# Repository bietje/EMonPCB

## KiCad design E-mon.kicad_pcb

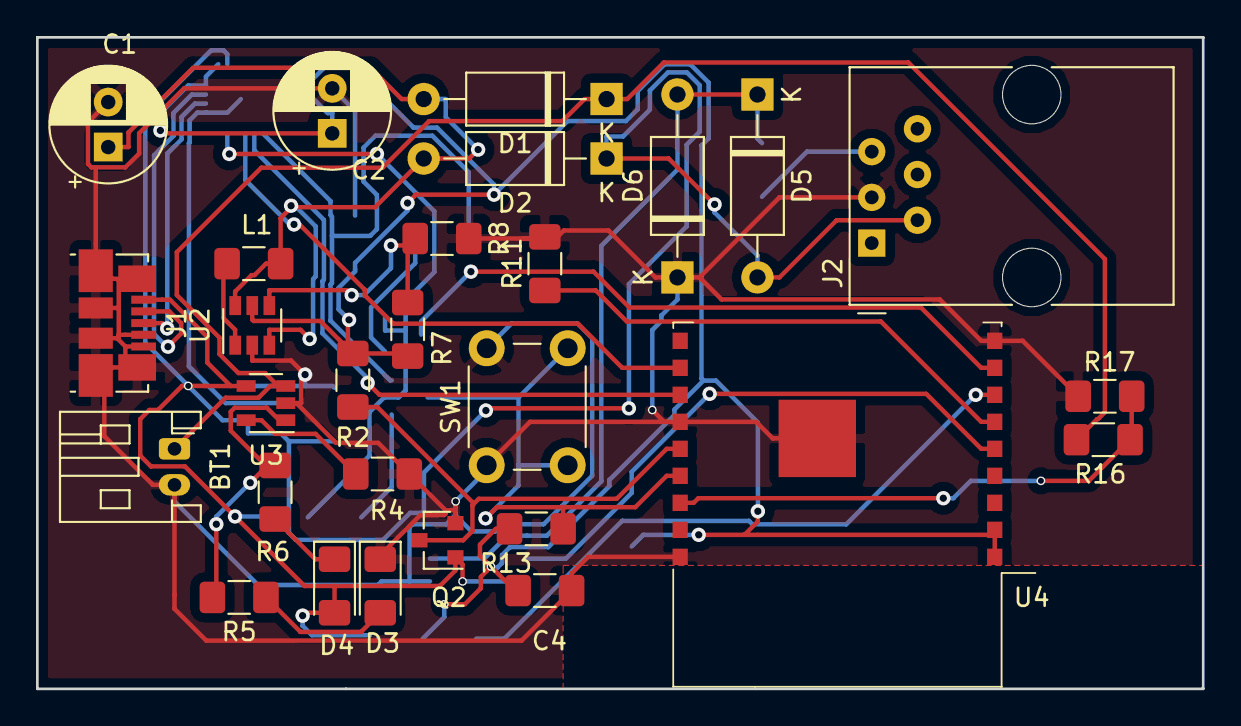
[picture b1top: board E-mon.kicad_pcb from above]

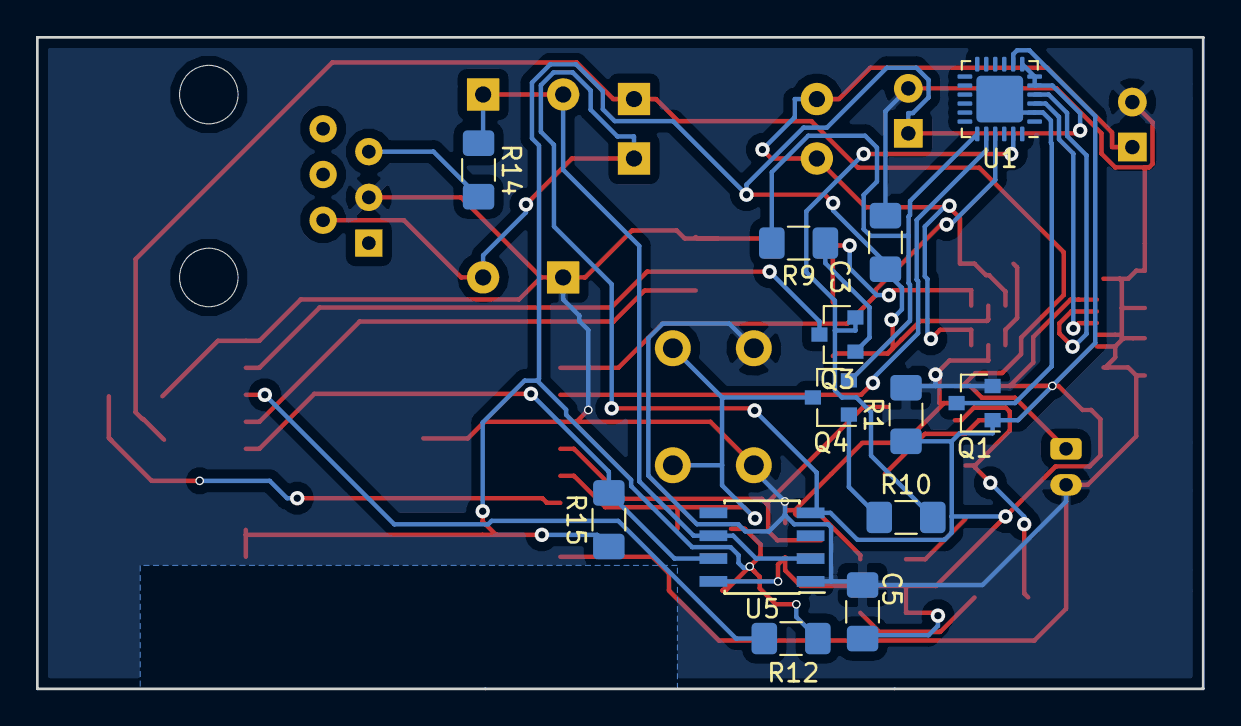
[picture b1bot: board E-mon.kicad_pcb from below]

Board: 2 copper layers, 64.8 x 36.2 mm, 41 parts (13 on the bottom side), 29 nets.

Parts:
BT1: Battery_Cell; JST_PH_S2B-PH-K_1x02_P2.00mm_Horizontal
C1: 4.7uF; CP_Radial_D6.3mm_P2.50mm
C2: 10uF; CP_Radial_D6.3mm_P2.50mm
C3, C4, C5: 100nF; C_1206_3216Metric_Pad1.42x1.75mm_HandSolder
D1, D2, D5, D6: DIODE; D_A-405_P10.16mm_Horizontal
D3: LED_ORANGE; LED_1206_3216Metric_Pad1.42x1.75mm_HandSolder
D4: LED_GREEN; LED_1206_3216Metric_Pad1.42x1.75mm_HandSolder
J1: USB_B_Micro; USB_Micro-B_Molex_47346-0001
J2: RJ18; RJ12_Amphenol_54601
L1: 4.7uH; L_1206_3216Metric_Pad1.42x1.75mm_HandSolder
Q1, Q2: MMBF170; SOT-23
Q3, Q4: MMBT5550L; SOT-23
R1, R2, R16, R17: 100kΩ; R_1206_3216Metric_Pad1.42x1.75mm_HandSolder
R4, R9, R10, R11, R12, R13: 10kΩ; R_1206_3216Metric_Pad1.42x1.75mm_HandSolder
R5, R6, R15: 1kΩ; R_1206_3216Metric_Pad1.42x1.75mm_HandSolder
R7: 976kΩ; R_1206_3216Metric_Pad1.42x1.75mm_HandSolder
R8: 562kΩ; R_1206_3216Metric_Pad1.42x1.75mm_HandSolder
R14: 200Ω; R_1206_3216Metric_Pad1.42x1.75mm_HandSolder
SW1: SW_Push; SW_PUSH_6mm
U1: CP2104; QFN-24-1EP_4x4mm_P0.5mm_EP2.6x2.6mm
U2: MCP1640BCH; SOT-23-6
U3: MCP73831-2-OT; SOT-23-5
U4: ESP-WROOM-02
U5: NE555; SOIC-8_3.9x4.9mm_P1.27mm

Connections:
+3V3: C2.1, C3.1, C4.1, R2.1, R7.1, R12.1, R13.1, R15.1, U1.5, U1.6, U1.7, U2.5, U4.1, U4.2
+BATT: BT1.1, D1.1, R16.1, U3.3
ADC: R16.2, R17.1, U4.16
DTR: Q3.2, R10.2, U1.23
D_NEG: J1.2, U1.4
D_PLUS: J1.3, U1.3
EMON_RX: R15.2, U4.5, U5.7
GND: BT1.2, C1.2, C2.2, C3.2, C4.2, C5.2, D3.1, D6.1, J1.4, J1.5, J1.6, J2.3, Q1.2, Q2.2, R1.2, R4.2, R8.2, R11.2, R17.2, SW1.1, U2.2, U3.2, U4.9, U4.13, U4.18, U4.19, U5.1
GPIO_0: Q3.3, U4.8
unnamed: C1.1, D1.2, D2.2, L1.1, U2.3, U2.6
unnamed: D3.2, R5.2
unnamed: D4.1, R6.2
unnamed: D5.1, D6.2, R14.1, U5.2, U5.6
unnamed: J2.5, R14.2
unnamed: L1.2, U2.1
unnamed: Q1.3, U1.2, U1.25
unnamed: Q3.1, R9.1
unnamed: Q4.1, R10.1
unnamed: R4.1, U3.5
unnamed: R5.1, R6.1, U3.1
unnamed: R7.2, R8.1, U2.4
unnamed: R11.1, U4.6
unnamed: R12.2, U4.7
PROG_RX0: U1.21, U4.11
PROG_TX0: U1.20, U4.12
RESET: Q4.3, R13.2, SW1.2, U4.15
RTS: Q4.2, R9.2, U1.19
VBUS: C5.1, D2.1, D4.2, D5.2, J1.1, J2.2, Q1.1, Q2.1, R1.1, U1.8, U3.4, U5.4, U5.8
Vadap: Q2.3, R2.2, U4.14

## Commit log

2019-04-12 project: add kicad project files
    Add initial project files and schematics.
2019-04-15 layout: add the board layout
    Implement a board layout in Pcbnew.
2019-04-15 pcb: fix various routing issues
    Fix some poorly routed tracks.
2019-04-15 pcb: add ground plane
    Add the ground plane to both layers.
2019-04-18 555: update Vcc connection of the NE555
    Connect the NE555 to the Vbus (5V) instead of 3.3V.
